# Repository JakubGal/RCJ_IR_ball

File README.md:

# RCJ_IR_ball
Opensource IR ball for robocup junior soccer

This project is still work in progress!!!

# TODO list:
1. Make a version of the drive board for self-assembly
2. Update switch to smd version for assembly
3. Change weight from current 89g to 95g with strengthening week parts of shelves
4. Make a panel version of all PCBs for kit
5. Create proper code with gyro auto turn-off feature
6. Check the avalibility of all components around the world
7. Test version with homemade PCBs
8. Make some ready-to-send kits for testing with 'early adopters'

# Quick guide on how to create your ball

## Stuff you nead
1. Every ball consists of 3 main parts:
2. Top and bottom shells
3. PCBs
4. Mechanical parts

## 1. Top and botom shells
To get your shells you can 3d print them yourself or ask a friend who has SLA 3d printer or order it from pcbway or another manufacturer with a 3d printing service. Here are some resins and manufacturers I tried if you found some other please open the issue and let us know so we can add it to a list.

|   | Resin name                | Were to buy | Cost per ball | Strenght | Transparenci | Photo |
|---|---------------------------|-------------|---------------|----------|--------------|-------|
| 1 |  Phrozen Aqva Resin Clear |[3djake](https://www.3djake.sk/liqcreate-resin-pre-sla-dlp-3d-tlaciarne/clear-impact) | 4,8 EUR| LOW  | MEDIUM||
| 2 |  Liqcreate Clear Impact   |[3djake](https://www.3djake.sk/liqcreate-resin-pre-sla-dlp-3d-tlaciarne/clear-impact)| 12,8 EUR| HIGH | MEDIUM| |
| 3 | UTR-8100                  |PCBWAY               |13,83 EUR|MEDIUM             | LOW      |
| 4 | UTR-8100(transparent)     |PCBWAY               |36,8 EUR|MEDIUM              |HIGH       |

## 2. PCBs
For PCBs, we have two main variants. One is cheaper and easier to make at home with just one switch, and the other with gyro, buzzer and ws2812b that can switch off itself when it will not move for 3 minutes. So you have 3 main options for how to get your PCBs:
1. Get them almost fully assembled by JLCPCB or PCBWAY (need to solder LEDs)
2. Get just PCBs and buy components from digikey/mouser/lcsc or other manufacturers and solder it all yourself (can choose simpler wersion of PCB so need for hot air station)
3. Make them and cut them all by yourself at home (need to order components) using photolithography or another process. TODO does detail guide on how to do that

### Components and where to get them
https://docs.google.com/spreadsheets/d/1AJk5qBYIz7-Oj68zrsEcClqDoz_VDrp_WEVsXvldfIE/edit#gid=0
(all componets are realy easy to get and they are in stock in at least 4 eshops)
TODO put in in table here
## 3. Mechanical parts
This is easiest part. You just need to buy folowing ithems from your local hardawe store or from internet(few sugested websides listed)
1. 2x M3 screw
2. 2x M3 nut
3. 8x brass/coperr standoff M3 10mm
TODO be more specifick and prowide links to websides were to get them

# Ball testing
When you make your ball now is the time to test if it actualy works. Here are few ways how to do that:

## Test quality of IR light
1. Use IR seeker (easy test with lego mindstor)
2. Use TSOP
3. Make your own ir seeker (link to repo how to meke your own ir seeker)
4. Use smartphone(not proof of working, just good assumption)

## Test mechanical integrity
1. dorop it form 1m and if it survives it is ok

## Test power consumption
1. Use ampere meter
2. Check if it have sam ir intensity for 3h (use new bateries)

Reference testing data:
https://drive.google.com/drive/folders/1isDrJiC3cLQZJ-q2lvDSGFadgaxJweIT?usp=share_link

TODO provide exact step by step how to test it with each metod

# How it works

TODO
Ball neads to emits ir light on wawelengt of 940nm in this modulated way:

to save energy a ...TODO
And drive PCB work like this.... TODO

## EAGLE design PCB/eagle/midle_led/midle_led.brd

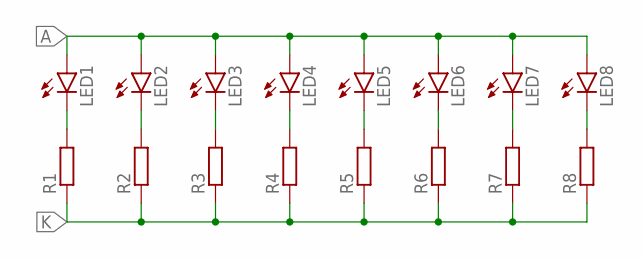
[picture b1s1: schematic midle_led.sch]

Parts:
LED1, LED2, LED3, LED4, LED5, LED6, LED7, LED8: LED5MM
R1, R2, R3, R4, R5, R6, R7, R8: R-EU_R0603; R0603

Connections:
A: LED1.A, LED2.A, LED3.A, LED4.A, LED5.A, LED6.A, LED7.A, LED8.A
K: R1.1, R2.1, R3.1, R4.1, R5.1, R6.1, R7.1, R8.1
unnamed: LED1.K (C), R1.2
unnamed: LED2.K (C), R2.2
unnamed: LED3.K (C), R3.2
unnamed: LED4.K (C), R4.2
unnamed: LED5.K (C), R5.2
unnamed: LED6.K (C), R6.2
unnamed: LED7.K (C), R7.2
unnamed: LED8.K (C), R8.2

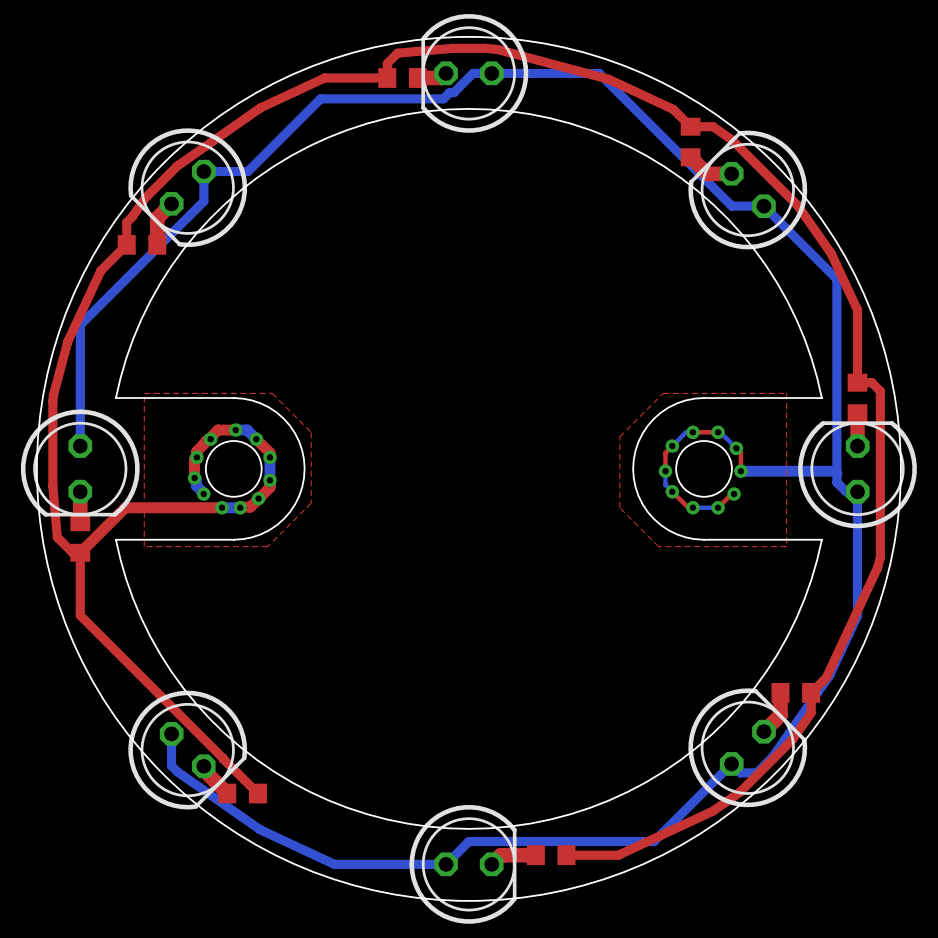
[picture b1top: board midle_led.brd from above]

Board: 2 copper layers, 48.0 x 48.0 mm, 16 parts (0 on the bottom side), 10 nets.

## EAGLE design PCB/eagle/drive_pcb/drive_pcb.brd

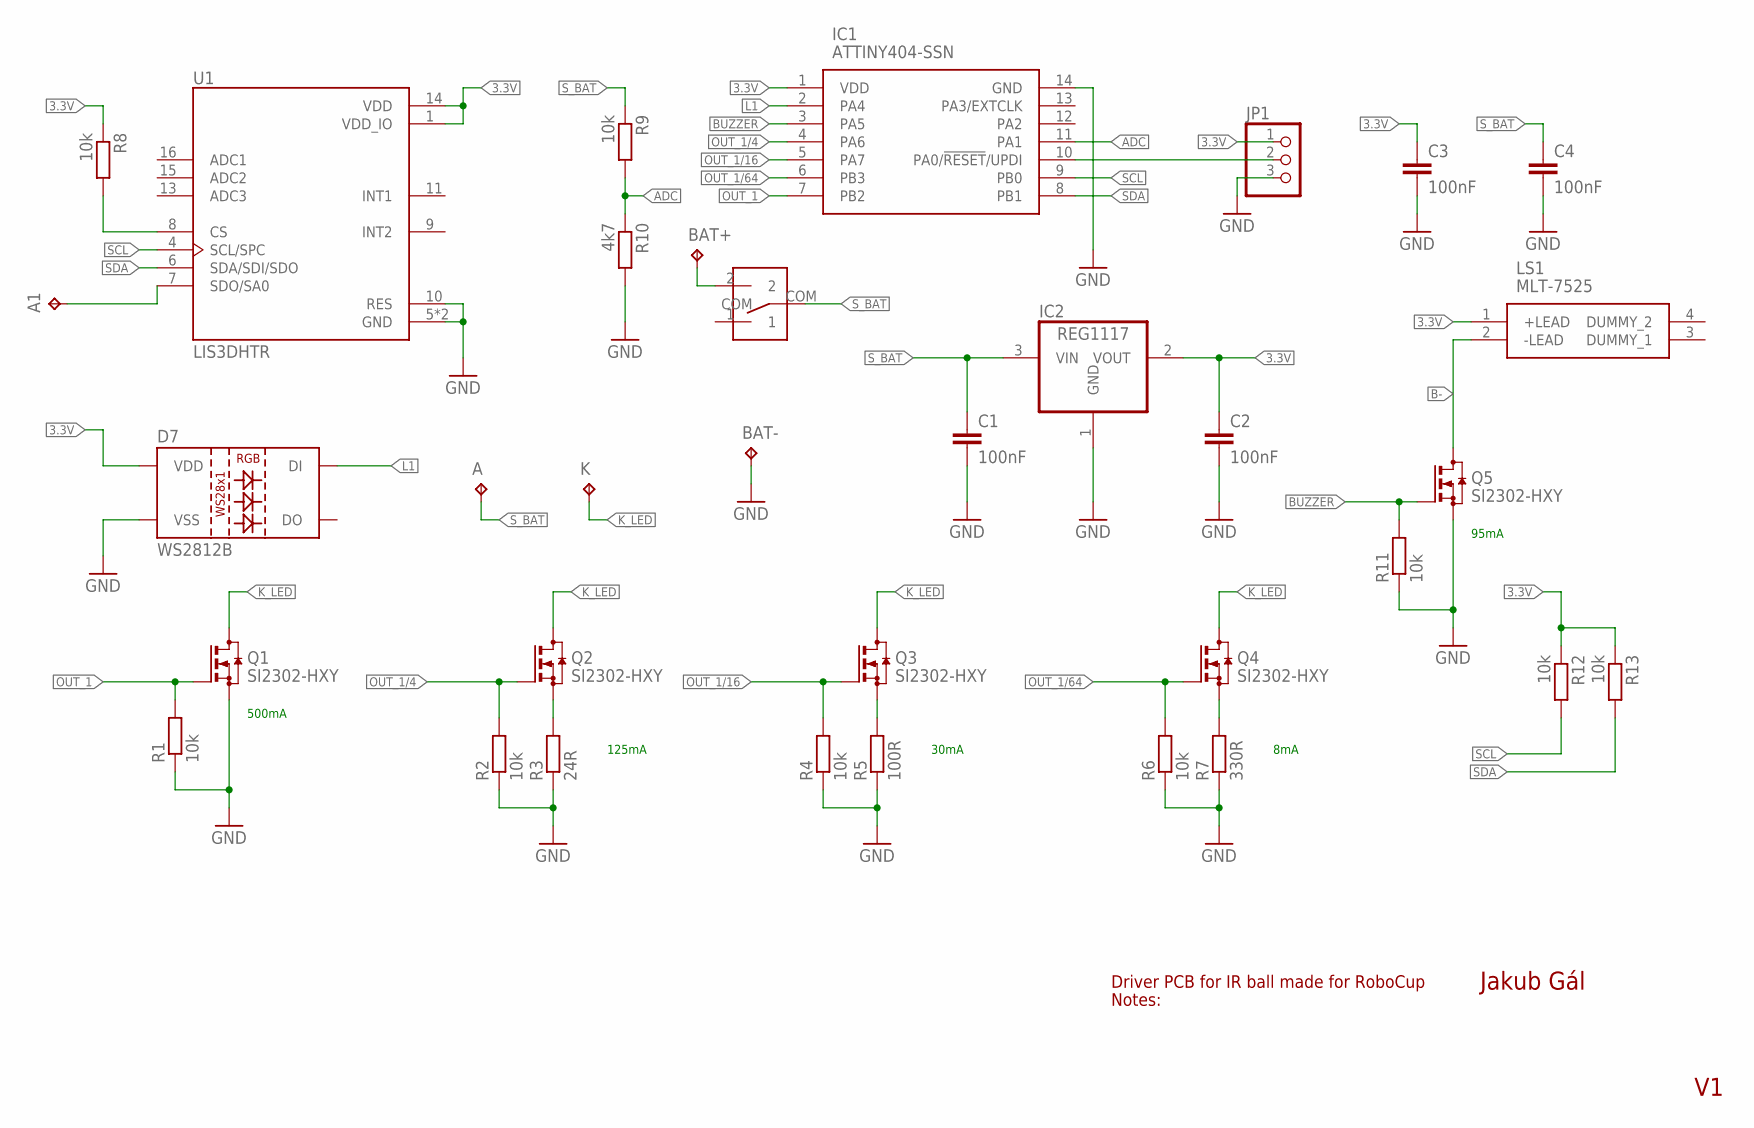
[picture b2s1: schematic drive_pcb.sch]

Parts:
A, A1: TPB1,27; B1,27
BAT+: TPB1,27; B1,27
BAT-: TPB1,27; B1,27
C1, C2, C3, C4: 100nF; C0603
D7: WS2812B
IC1: ATTINY404-SSN; SOIC127P600X175-14N
IC2: REG1117; SOT223
JP1: PINHD-1X3; 1X03
K: TPB1,27; B1,27
LS1: MLT-7525; MLT7525
Q1, Q2, Q3, Q4, Q5: SI2302-HXY; SOT23
R1, R2, R4, R6, R8, R9, R11, R12, R13: 10k; R0603
R3: 24R; R0603
R5: 100R; R0603
R7: 330R; R0603
R10: 4k7; R0603
U1: LIS3DHTR; XDCR_LIS3DHTR
U$1: SK12D07VG4

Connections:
3.3V: C2.1, C3.1, D7.1 (VDD), IC1.1 (VDD), IC2.2 (VOUT), JP1.1, LS1.1 (+LEAD), R8.1, R12.1, R13.1, U1.1 (VDD_IO), U1.14 (VDD)
ADC: IC1.11 (PA1), R9.2, R10.1
B-: LS1.2 (-LEAD), Q5.3 (D)
BUZZER: IC1.3 (PA5), Q5.1 (G), R11.2
GND: BAT-.TP, C1.2, C2.2, C3.2, C4.2, D7.3 (VSS), IC1.14 (GND), IC2.1 (GND), JP1.3, Q1.2 (S), Q5.2 (S), R1.1, R2.1, R3.1, R4.1, R5.1, R6.1, R7.1, R10.2, R11.1, U1.5 (GND), U1.10 (RES), U1.12 (GND)
K_LED: K.TP, Q1.3 (D), Q2.3 (D), Q3.3 (D), Q4.3 (D)
L1: D7.4 (DI), IC1.2 (PA4)
unnamed: Q2.2 (S), R3.2
unnamed: Q3.2 (S), R5.2
unnamed: Q4.2 (S), R7.2
unnamed: R8.2, U1.8 (CS)
unnamed: IC1.10 (PA0/!RESET!/UPDI), JP1.2
unnamed: A1.TP, U1.7 (SDO/SA0)
unnamed: BAT+.TP, U$1.2
OUT_1: IC1.7 (PB2), Q1.1 (G), R1.2
OUT_1/4: IC1.4 (PA6), Q2.1 (G), R2.2
OUT_1/16: IC1.5 (PA7), Q3.1 (G), R4.2
OUT_1/64: IC1.6 (PB3), Q4.1 (G), R6.2
SCL: IC1.9 (PB0), R12.2, U1.4 (SCL/SPC)
SDA: IC1.8 (PB1), R13.2, U1.6 (SDA/SDI/SDO)
S_BAT: A.TP, C1.1, C4.1, IC2.3 (VIN), R9.1, U$1.COM

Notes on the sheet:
500mA
125mA
30mA
8mA
95mA
Jakub Gál
Driver PCB for IR ball made for RoboCup
Notes:

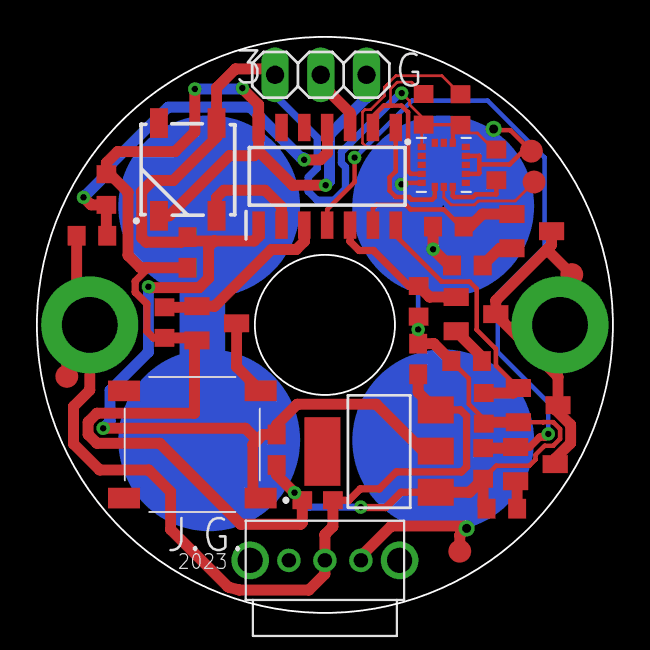
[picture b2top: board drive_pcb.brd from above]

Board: 2 copper layers, 32.0 x 32.0 mm, 34 parts (0 on the bottom side), 21 nets.

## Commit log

2023-02-10 first
2023-02-10 code
2023-02-10 readme

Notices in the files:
parts and their libraries:
SparkFun-LED: Licensing: Creative Commons ShareAlike 4.0 International - https://creativecommons.org/licenses/by-sa/4.0
